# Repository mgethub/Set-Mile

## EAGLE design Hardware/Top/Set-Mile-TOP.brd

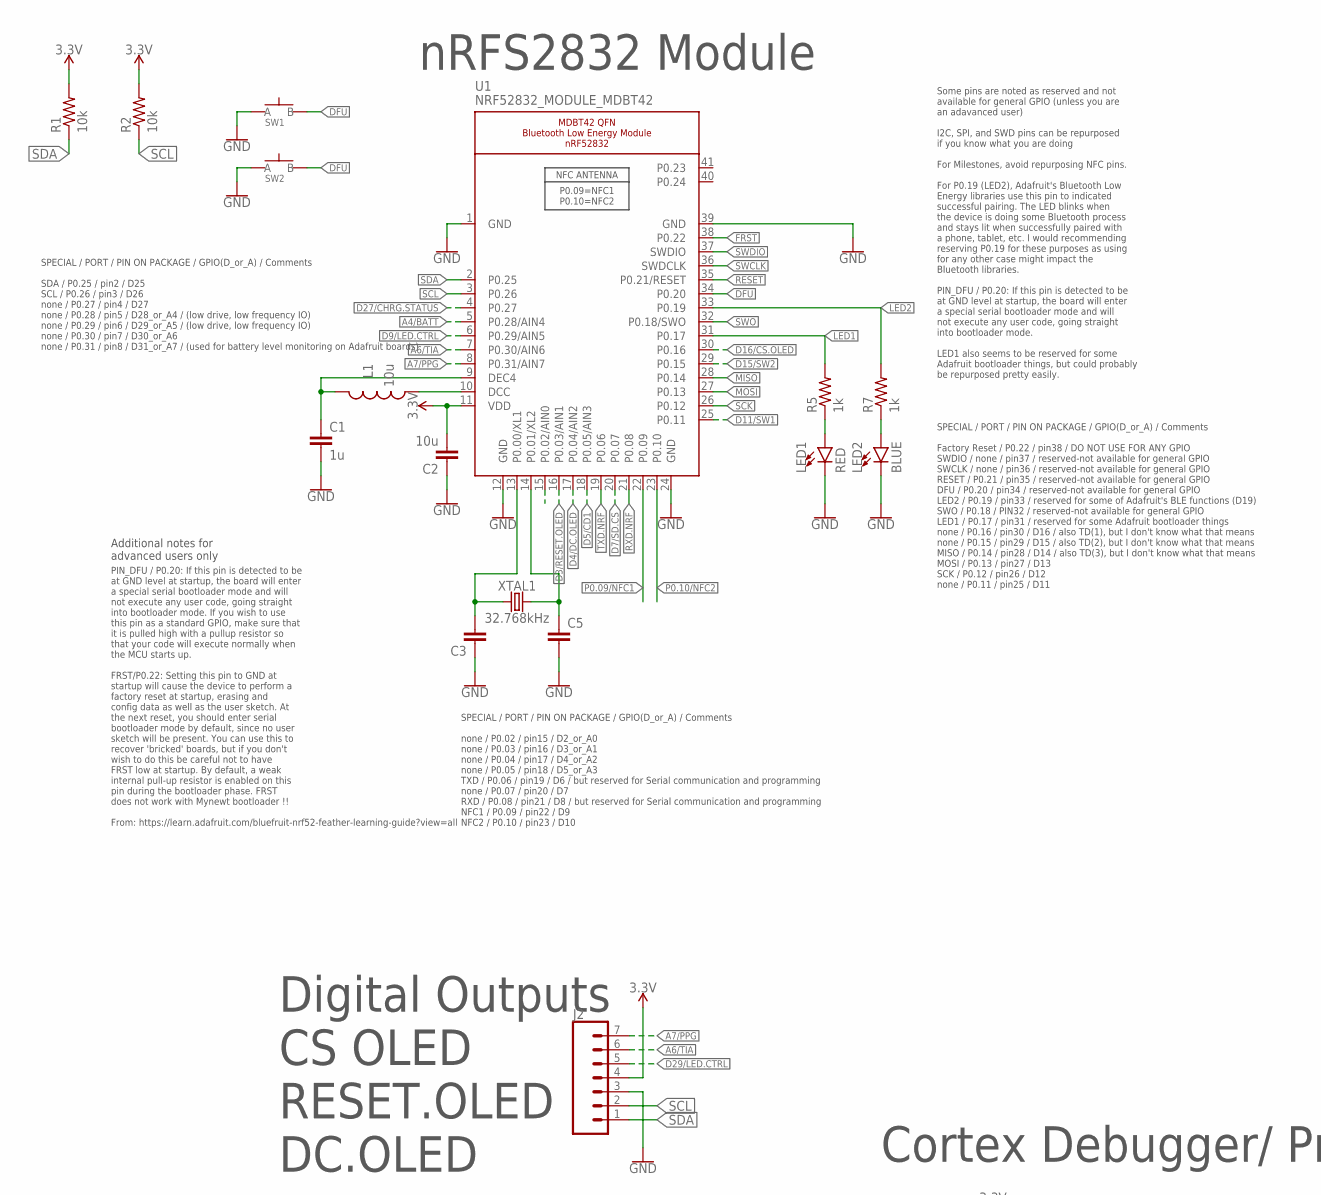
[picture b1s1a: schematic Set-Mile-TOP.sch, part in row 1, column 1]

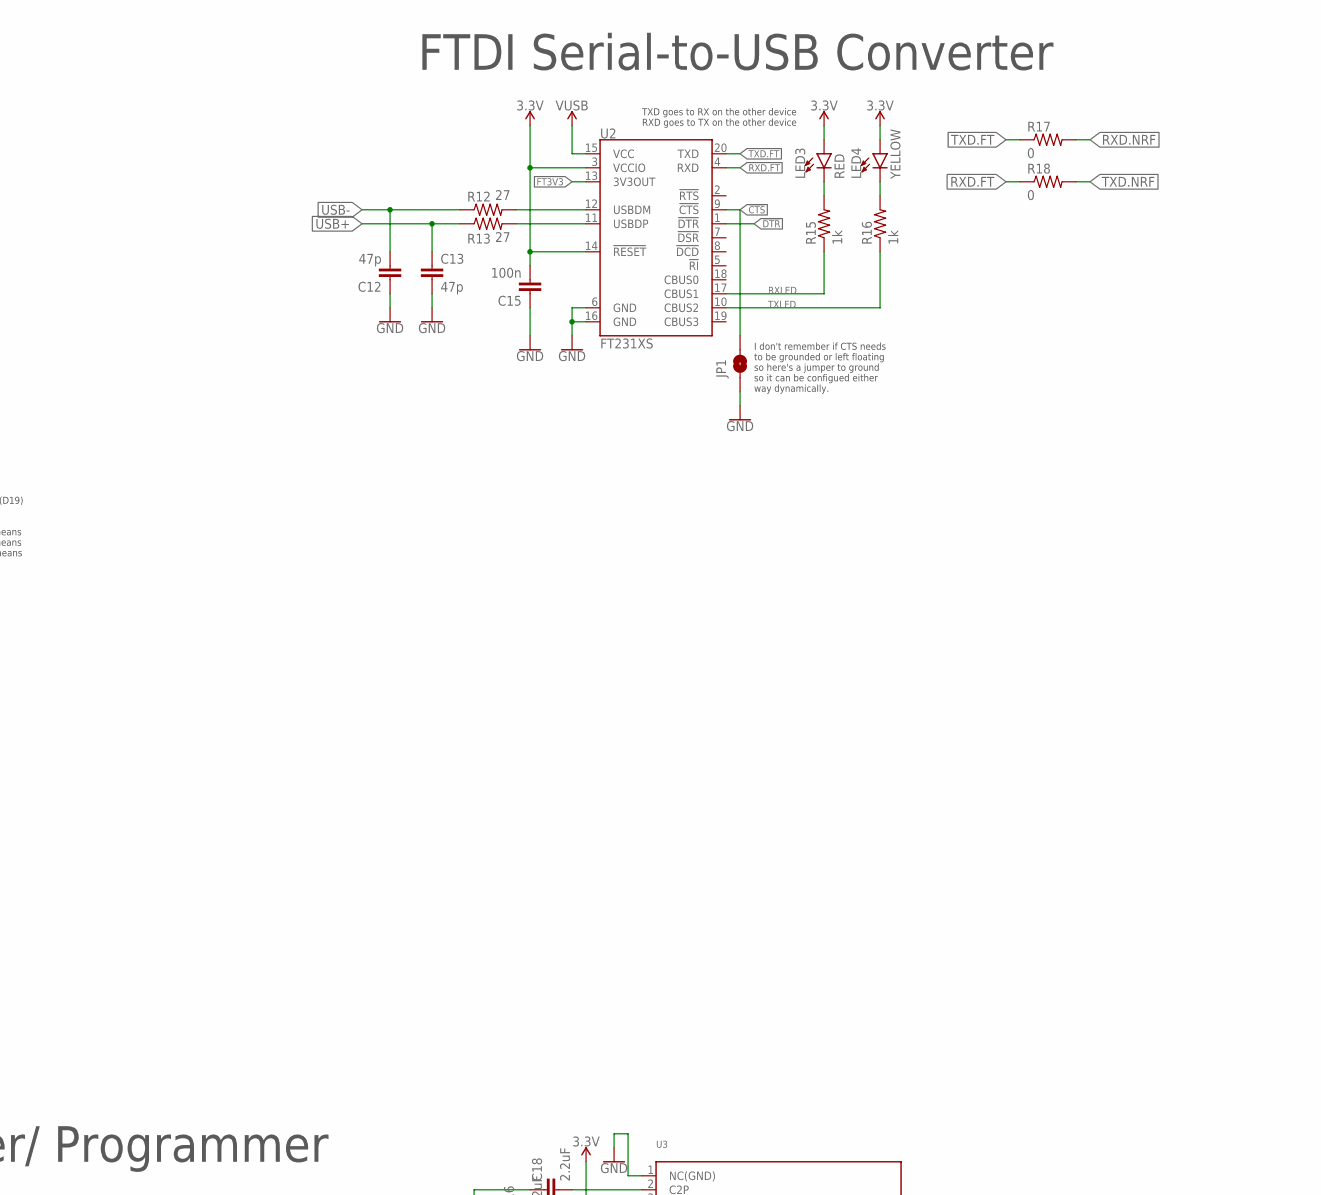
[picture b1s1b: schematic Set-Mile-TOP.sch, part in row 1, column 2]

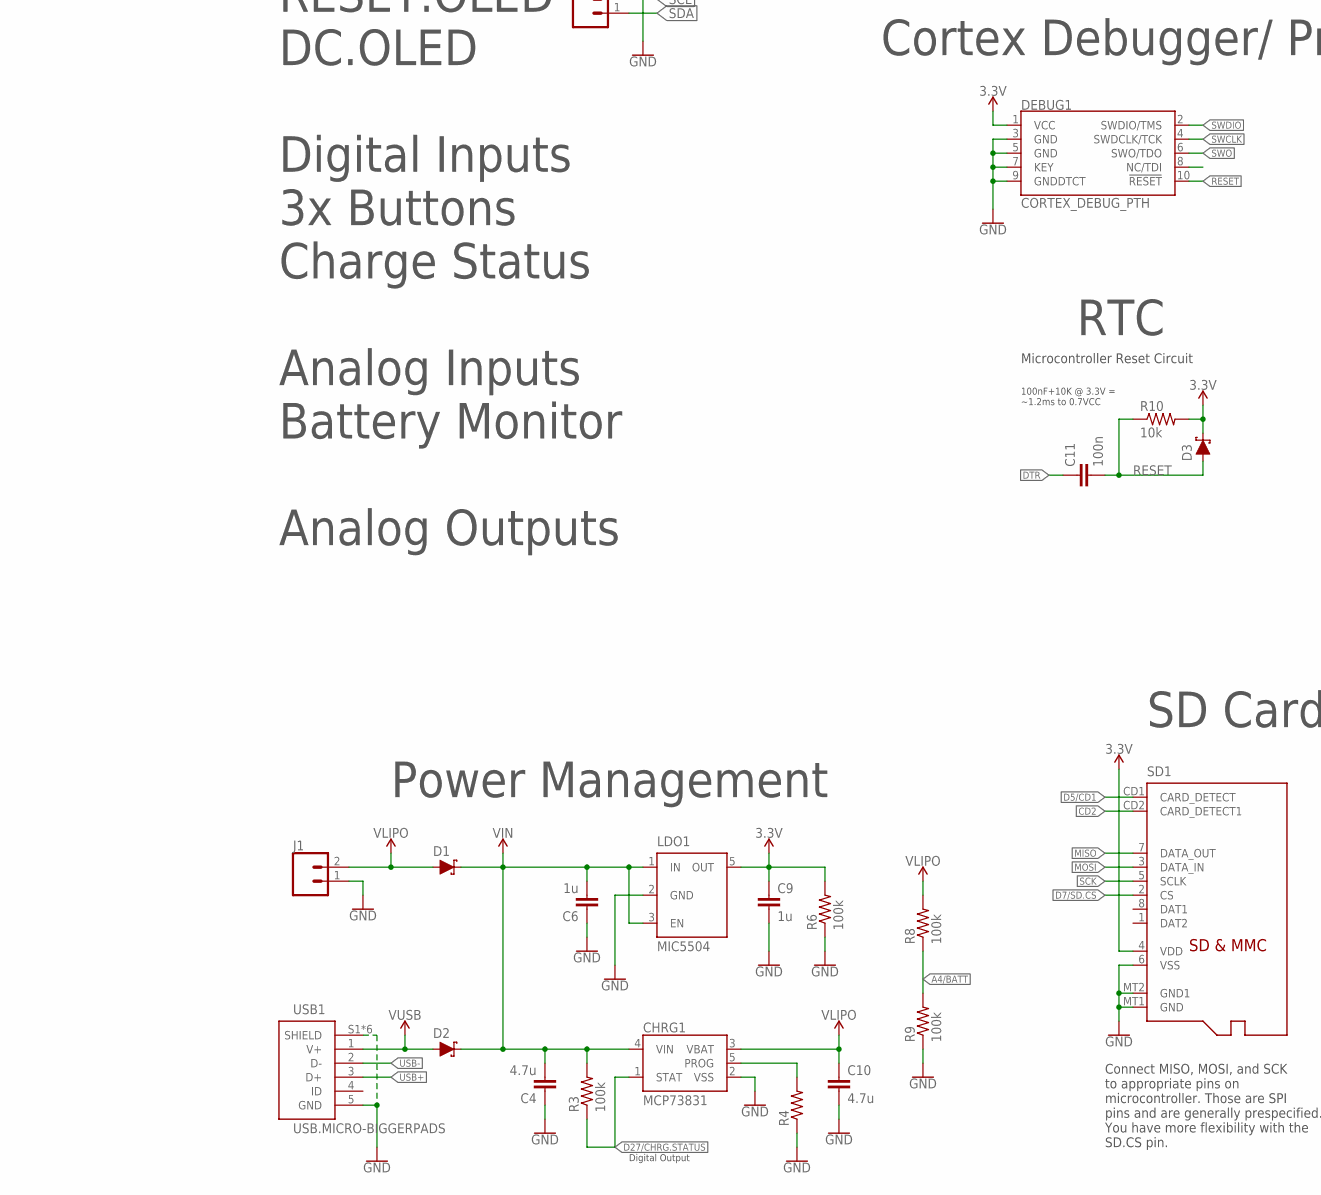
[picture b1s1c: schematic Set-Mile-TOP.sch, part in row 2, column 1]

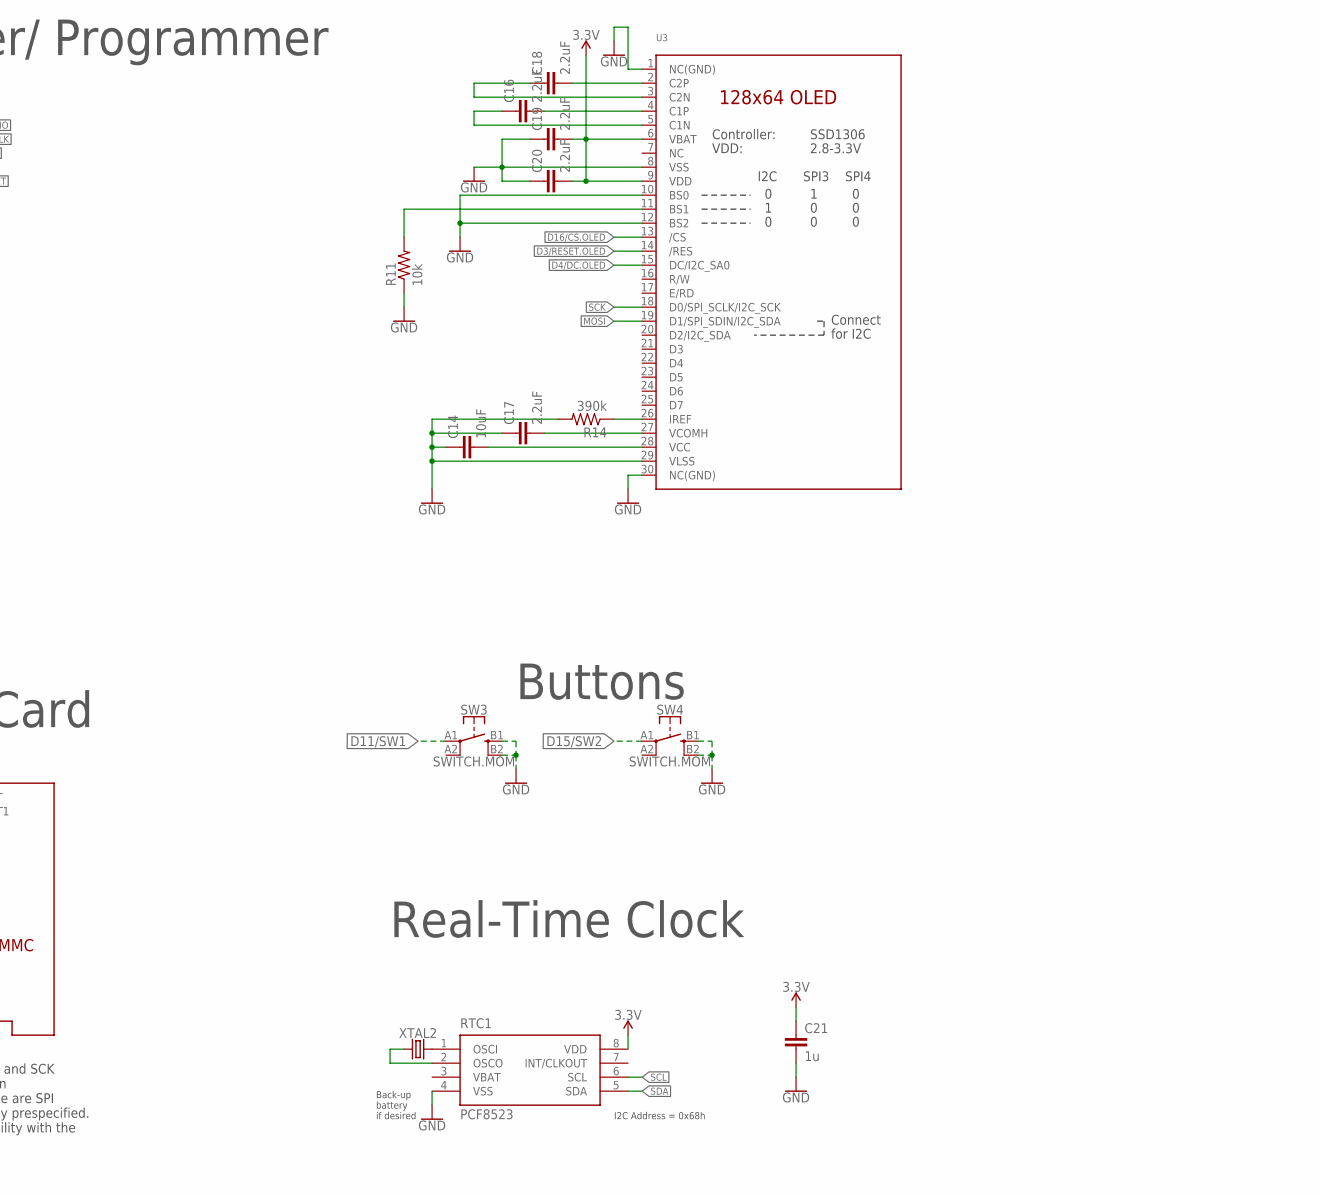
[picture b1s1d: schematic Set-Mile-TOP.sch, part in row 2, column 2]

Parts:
C1, C6, C9, C21: 1u; C0603
C2: 10u; C0805
C3, C5: CAPACITOR0603; C0603
C4, C10: 4.7u; C0603
C11, C15: 100n; C0603
C12, C13: 47p; C0603
C14: 10uF; C0603
C16, C17, C18, C19, C20: 2.2uF; C0402
CHRG1: MCP73831; SOT23-5
D1, D2, D3: SCHOTTKY-USC; USC
DEBUG1: CORTEX_DEBUG_PTH; 2X5-PTH-1.27MM
J1: CONN_02; 1X02
J2: CONN_07-1.27MM; 1X07_1.27MM
JP1: JUMPER-SMT_2_NO_SILK; SMT-JUMPER_2_NO_SILK
L1: 10u; L0603
LDO1: MIC5504; SOT23-5
LED1, LED3: RED; LED-0603
LED2: BLUE; LED-0603
LED4: YELLOW; LED-0603
R1, R2, R10, R11: 10k; R0603
R3, R6, R8, R9: 100k; R0603
R4: RESISTOR0603; R0603
R5, R7, R15, R16: 1k; R0603
R12, R13: 27; R0603
R14: 390k; R0603
R17, R18: 0; R0603
RTC1: PCF8523; SO8; DIGIKEY 568-5306-1-ND
SD1: MICROSD
SW1, SW2: SPST-PTS830GG140-COPY.1-3; BUTTON-GULLWING
SW3, SW4: SWITCH.MOM; TACTILE_SWITCH_SMD_6.2MM_TALL
U1: NRF52832_MODULE_MDBT42; BLE_MODULE_RAYTAC_MDBT42
U2: FT231XS; SSOP20_L
U3: DISP_OLED_UG-2864HSWEG01-NO-WRAPAROUND; UG-2864HSWEG01_0.96IN_NO-WRAPAROUND
USB1: USB.MICRO-BIGGERPADS; USB-MICRO-01.BIGGERPADS
XTAL1: 32.768kHz; 2-SMD.NOLEAD.2.0MMTO1.2MM
XTAL2: 32.7680kHz; 2-SMD.NOLEAD.2.0MMTO1.2MM

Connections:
3.3V: C2.2, C9.1, C15.2, C19.2, C20.2, C21.1, D3.- (C), DEBUG1.1 (VCC), J2.4, LDO1.5 (OUT), LED3.A, LED4.A, R1.2, R2.2, R6.2, R10.2, RTC1.8 (VDD), SD1.4 (VDD), U1.11 (VDD), U2.3 (VCCIO), U2.14 (!RESET), U3.6 (VBAT), U3.9 (VDD)
!CTS: JP1.2, U2.9 (!CTS)
!DTR: U2.1 (!DTR)
A4/BATT: R8.1, R9.2, U1.5 (P0.28/AIN4)
A6/TIA: J2.6, U1.7 (P0.30/AIN6)
A7/PPG: J2.7, U1.8 (P0.31/AIN7)
CD2: SD1.CD2 (CARD_DETECT1)
D3/RESET.OLED: U1.16 (P0.03/AIN1), U3.14 (/RES)
D4/DC.OLED: U1.15 (P0.02/AIN0), U1.17 (P0.04/AIN2), U3.15 (DC/I2C_SA0)
D5/CD1: SD1.CD1 (CARD_DETECT), U1.18 (P0.05/AIN3)
D7/SD.CS: SD1.2 (CS), U1.20 (P0.07)
D9/LED.CTRL: U1.6 (P0.29/AIN5)
D11/SW1: SW3.A1 (1), U1.25 (P0.11)
D15/SW2: SW4.A1 (1), U1.29 (P0.15)
D16/CS.OLED: U1.30 (P0.16), U3.13 (/CS)
D27/CHRG.STATUS: CHRG1.1 (STAT), R3.1, U1.4 (P0.27)
D29/LED.CTRL: J2.5
DFU: SW1.3 (B), SW2.3 (B), U1.34 (P0.20)
DTR: C11.1
FRST: U1.38 (P0.22)
FT3V3: U2.13 (3V3OUT)
GND: C1.2, C2.1, C3.1, C4.1, C5.2, C6.1, C9.2, C10.2, C12.1, C13.2, C14.1, C15.1, C17.1, C19.1, C20.1, C21.2, CHRG1.2 (VSS), DEBUG1.3 (GND), DEBUG1.5 (GND), DEBUG1.7 (KEY), DEBUG1.9 (GNDDTCT), J1.1, J2.3, JP1.1, LDO1.2 (GND), LED1.C, LED2.C, R4.1, R6.1, R9.1, R11.1, R14.2, RTC1.4 (VSS), SD1.6 (VSS), SD1.MT1 (GND), SD1.MT2 (GND1), SW1.1 (A), SW2.1 (A), SW3.B1 (3), SW3.B2 (4), SW4.B1 (3), SW4.B2 (4), U1.1 (GND), U1.12 (GND), U1.24 (GND), U1.39 (GND), U2.6 (GND), U2.16 (GND), U3.1 (NC(GND)), U3.8 (VSS), U3.10 (BS0), U3.12 (BS2), U3.29 (VLSS), U3.30 (NC(GND)), USB1.5 (GND), USB1.S1 (SHIELD), USB1.S2 (SHIELD), USB1.S3 (SHIELD), USB1.S4 (SHIELD), USB1.S5 (SHIELD), USB1.S6 (SHIELD)
LED1: R5.2, U1.31 (P0.17)
LED2: R7.2, U1.33 (P0.19)
MISO: SD1.7 (DATA_OUT), U1.28 (P0.14)
MOSI: SD1.3 (DATA_IN), U1.27 (P0.13), U3.19 (D1/SPI_SDIN/I2C_SDA)
unnamed: R11.2, U3.11 (BS1)
unnamed: R14.1, U3.26 (IREF)
unnamed: C18.2, U3.2 (C2P)
unnamed: C3.2, U1.13 (P0.00/XL1), XTAL1.P$1 (1)
unnamed: C18.1, U3.3 (C2N)
unnamed: C5.1, U1.14 (P0.01/XL2), XTAL1.P$2 (2)
unnamed: C16.2, U3.4 (C1P)
unnamed: C16.1, U3.5 (C1N)
unnamed: LED1.A, R5.1
unnamed: LED2.A, R7.1
unnamed: L1.1, U1.10 (DCC)
unnamed: C1.1, L1.2, U1.9 (DEC4)
unnamed: C14.2, U3.28 (VCC)
unnamed: C17.2, U3.27 (VCOMH)
unnamed: CHRG1.5 (PROG), R4.2
unnamed: RTC1.2 (OSCO), XTAL2.P$1 (1)
unnamed: RTC1.1 (OSCI), XTAL2.P$2 (2)
unnamed: R12.2, U2.12 (USBDM)
unnamed: R13.2, U2.11 (USBDP)
unnamed: LED3.C, R15.2
unnamed: LED4.C, R16.2
P0.09/NFC1: U1.22 (P0.09)
P0.10/NFC2: U1.23 (P0.10)
RESET: C11.2, D3.+ (A), DEBUG1.10 (!RESET), R10.1, U1.35 (P0.21/RESET)
RXD.FT: R18.1, U2.4 (RXD)
RXD.NRF: R17.2, U1.21 (P0.08)
RXLED: R15.1, U2.17 (CBUS1)
SCK: SD1.5 (SCLK), U1.26 (P0.12), U3.18 (D0/SPI_SCLK/I2C_SCK)
SCL: J2.2, R2.1, RTC1.6 (SCL), U1.3 (P0.26)
SDA: J2.1, R1.1, RTC1.5 (SDA), U1.2 (P0.25)
SWCLK: DEBUG1.4 (SWDCLK/TCK), U1.36 (SWDCLK)
SWDIO: DEBUG1.2 (SWDIO/TMS), U1.37 (SWDIO)
SWO: DEBUG1.6 (SWO/TDO), U1.32 (P0.18/SWO)
TXD.FT: R17.1, U2.20 (TXD)
TXD.NRF: R18.2, U1.19 (P0.06)
TXLED: R16.1, U2.10 (CBUS2)
USB+: C13.1, R13.1, USB1.3 (D+)
USB-: C12.2, R12.1, USB1.2 (D-)
VIN: C4.2, C6.2, CHRG1.4 (VIN), D1.- (C), D2.- (C), LDO1.1 (IN), LDO1.3 (EN), R3.2
VLIPO: C10.1, CHRG1.3 (VBAT), D1.+ (A), J1.2, R8.2
V_USB: D2.+ (A), U2.15 (VCC), USB1.1 (V+)

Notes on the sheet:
Microcontroller Reset Circuit
100nF+10K @ 3.3V = ~1.2ms to 0.7VCC
SPECIAL / PORT / PIN ON PACKAGE / GPIO(D_or_A) / Comments SDA / P0.25 / pin2 / D25 SCL / P0.26 / pin3 / D26 none / P0.27 / pin4 / D27 none / P0.28 / pin5 / D28_or_A4 / (low drive, low frequency IO) none / P0.29 / pin6 / D29_or_A5 / (low drive, low frequency IO) none / P0.30 / pin7 / D30_or_A6 none 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
SPECIAL / PORT / PIN ON PACKAGE / GPIO(D_or_A) / Comments none / P0.02 / pin15 / D2_or_A0 none / P0.03 / pin16 / D3_or_A1 none / P0.04 / pin17 / D4_or_A2 none / P0.05 / pin18 / D5_or_A3 TXD / P0.06 / pin19 / D6 / but reserved for Serial communication and programming none / P0.07 / pin20 / D7 RXD / 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
SPECIAL / PORT / PIN ON PACKAGE / GPIO(D_or_A) / Comments Factory Reset / P0.22 / pin38 / DO NOT USE FOR ANY GPIO SWDIO / none / pin37 / reserved-not available for general GPIO SWCLK / none / pin36 / reserved-not available for general GPIO RESET / P0.21 / pin35 / reserved-not available for general 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
Some pins are noted as reserved and not available for general GPIO (unless you are an adavanced user) I2C, SPI, and SWD pins can be repurposed if you know what you are doing For Milestones, avoid repurposing NFC pins. For P0.19 (LED2), Adafruit's Bluetooth Low Energy libraries use this pin to indic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
PIN_DFU / P0.20: If this pin is detected to be at GND level at startup, the board will enter a special serial bootloader mode and will not execute any user code, going straight into bootloader mode. If you wish to use this pin as a standard GPIO, make sure that it is pulled high with a pullup resis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
Additional notes for advanced users only
Connect MISO, MOSI, and SCK to appropriate pins on microcontroller. Those are SPI pins and are generally prespecified. You have more flexibility with the SD.CS pin.
I2C Address = 0x68h
Back-up battery if desired
SD Card
nRFS2832 Module
Real-Time Clock
RTC
Cortex Debugger/ Programmer
Power Management
Buttons
Digital Outputs CS OLED RESET.OLED DC.OLED Digital Inputs 3x Buttons Charge Status Analog Inputs Battery Monitor Analog Outputs
TXD goes to RX on the other device RXD goes to TX on the other device
I don't remember if CTS needs to be grounded or left floating so here's a jumper to ground so it can be configued either way dynamically.
FTDI Serial-to-USB Converter
Digital Output

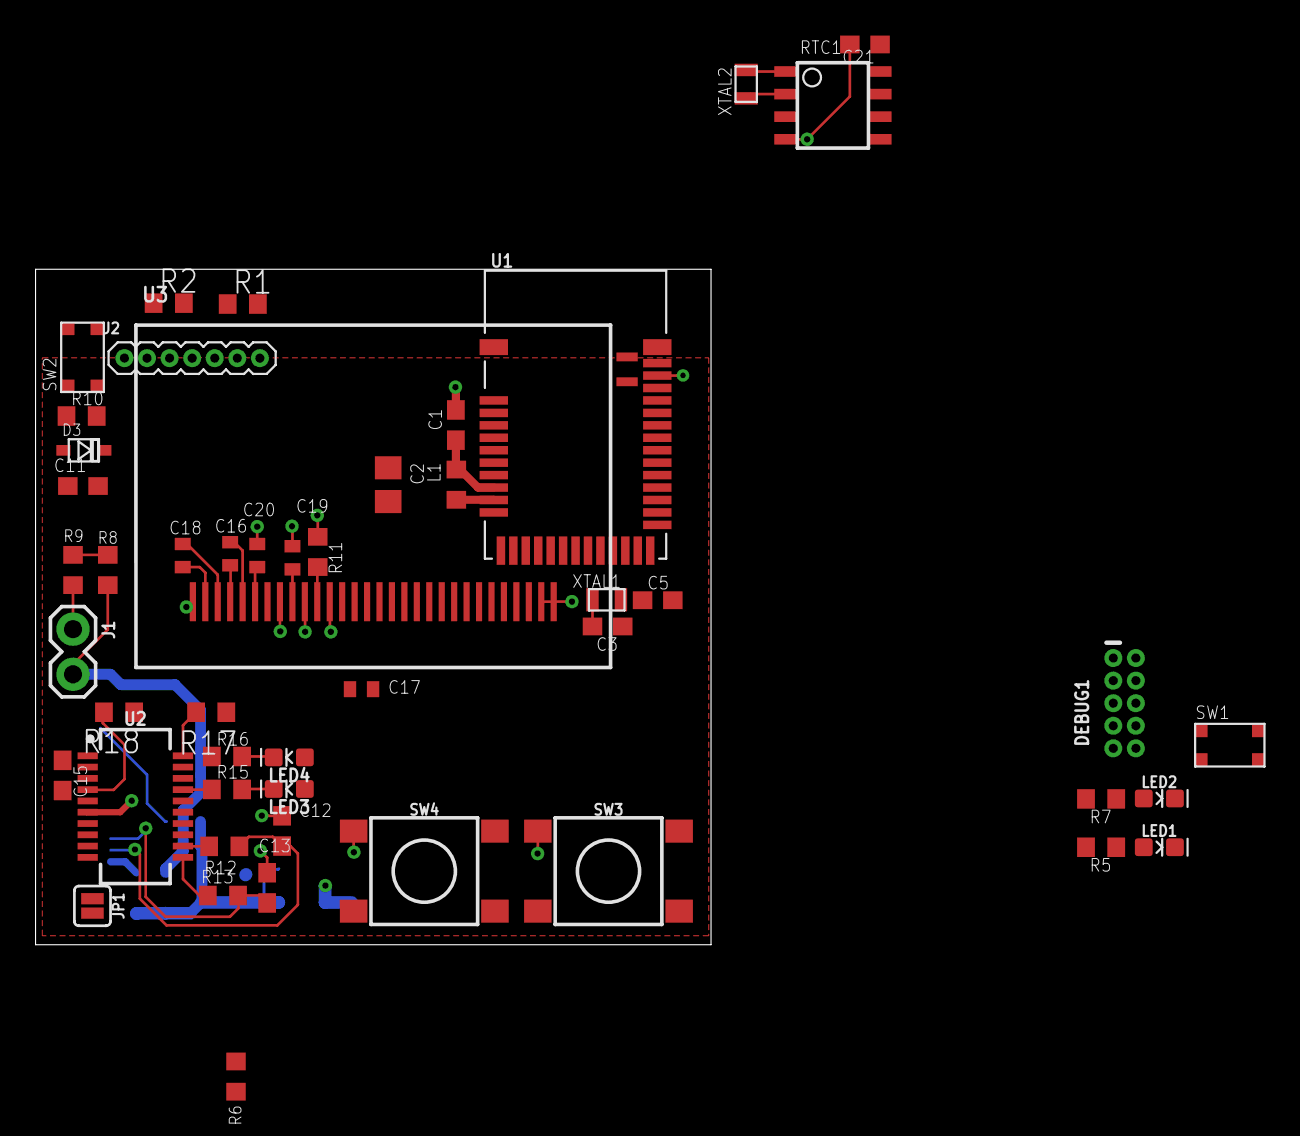
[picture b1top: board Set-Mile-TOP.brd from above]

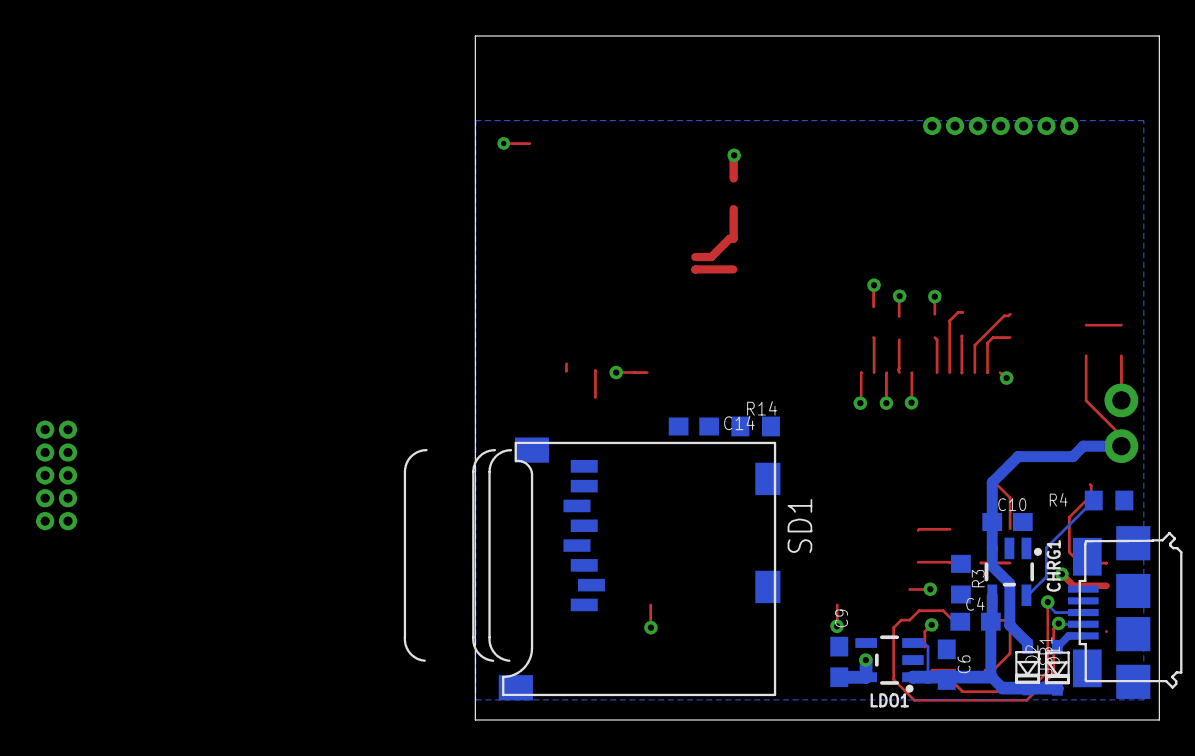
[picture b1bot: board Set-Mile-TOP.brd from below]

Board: 2 copper layers, 38.0 x 38.0 mm, 63 parts (14 on the bottom side), 58 nets.

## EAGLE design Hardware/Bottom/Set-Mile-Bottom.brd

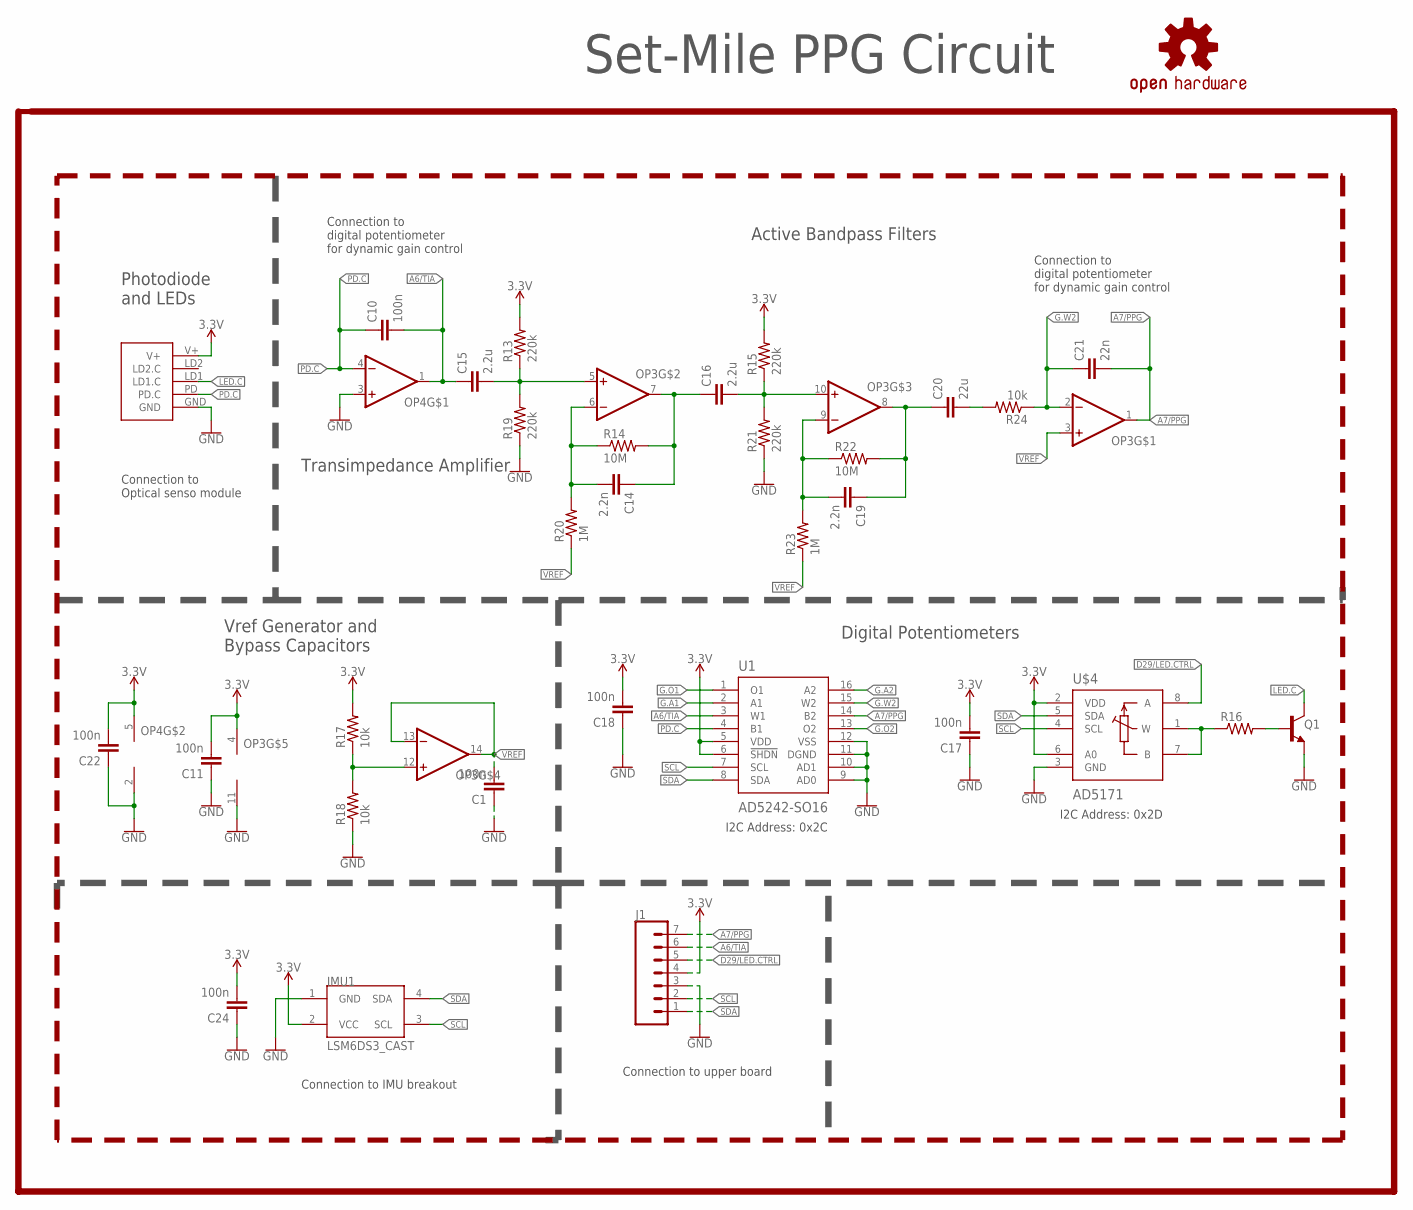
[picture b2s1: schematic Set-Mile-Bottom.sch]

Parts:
C1, C10, C11, C17, C18, C22, C24: 100n; C0603
C14, C19: 2.2n; C0603
C15, C16: 2.2u; C0603
C20: 22u; C0603
C21: 22n; C0603
IMU1: LSM6DS3_CAST
J1: CONN_07-1.27MM; 1X07_1.27MM
LOGO1: REVISION.A; REV.A
LOGO2: OSHW-LOGOL; OSHW-LOGO-L
OP3: OP-QUAD-SO14; SO14
OP4: OP-SINGLEOT; SOT23-5
Q1: NPN-GENERIC; SOT23-3
R13, R15, R19, R21: 220k; R0603
R14, R22: 10M; R0603
R16: RESISTOR0603; R0603
R17, R18: 10k; R0402
R20, R23: 1M; R0603
R24: 10k; R0603
U1: AD5242-SO16; SO16
U$3: PPG.MODULE.2
U$4: AD5171; SOT-23-8

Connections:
3.3V: C11.2, C17.2, C18.2, C22.2, C24.2, IMU1.2 (VCC), J1.4, OP3.4 (V+), OP4.5 (V+), R13.2, R15.2, R17.2, U1.5 (VDD), U1.6 (!SHDN), U$3.V+, U$4.2 (VDD), U$4.6 (A0)
A6/TIA: C10.2, C15.1, J1.6, OP4.1 (OUT), U1.3 (W1)
A7/PPG: C21.2, J1.7, OP3.1 (OUT), U1.14 (B2)
D29/LED.CTRL: J1.5, U$4.8 (A)
G.A1: U1.2 (A1)
G.A2: U1.16 (A2)
G.O1: U1.1 (O1)
G.O2: U1.13 (O2)
G.W2: C21.1, OP3.2 (-IN), R24.1, U1.15 (W2)
GND: C1.1, C11.1, C17.1, C18.1, C22.1, C24.1, IMU1.1 (GND), J1.3, OP3.11 (V-), OP4.2 (V-), OP4.3 (+IN), Q1.2 (E), R18.1, R19.1, R21.1, U1.9 (AD0), U1.10 (AD1), U1.11 (DGND), U1.12 (VSS), U$3.GND, U$4.3 (GND)
LED.C: Q1.3 (C), U$3.LD1 (LD1.C)
unnamed: Q1.1 (B), R16.2
unnamed: R16.1, U$4.1 (W), U$4.7 (B)
unnamed: OP3.12 (+IN), R17.1, R18.2
unnamed: C15.2, OP3.5 (+IN), R13.1, R19.2
unnamed: C14.2, OP3.6 (-IN), R14.1, R20.2
unnamed: C14.1, C16.1, OP3.7 (OUT), R14.2
unnamed: C16.2, OP3.10 (+IN), R15.1, R21.2
unnamed: C19.2, OP3.9 (-IN), R22.1, R23.2
unnamed: C19.1, C20.1, OP3.8 (OUT), R22.2
unnamed: C20.2, R24.2
PD.C: C10.1, OP4.4 (-IN), U1.4 (B1), U$3.PD (PD.C)
SCL: IMU1.3 (SCL), J1.2, U1.7 (SCL), U$4.4 (SCL)
SDA: IMU1.4 (SDA), J1.1, U1.8 (SDA), U$4.5 (SDA)
VREF: C1.2, OP3.3 (+IN), OP3.13 (-IN), OP3.14 (OUT), R20.1, R23.1

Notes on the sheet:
Photodiode and LEDs
Active Bandpass Filters
Digital Potentiometers
Transimpedance Amplifier
I2C Address: 0x2C
I2C Address: 0x2D
Connection to Optical senso module
Connection to digital potentiometer for dynamic gain control
Connection to upper board
Connection to IMU breakout
Vref Generator and Bypass Capacitors
Set-Mile PPG Circuit

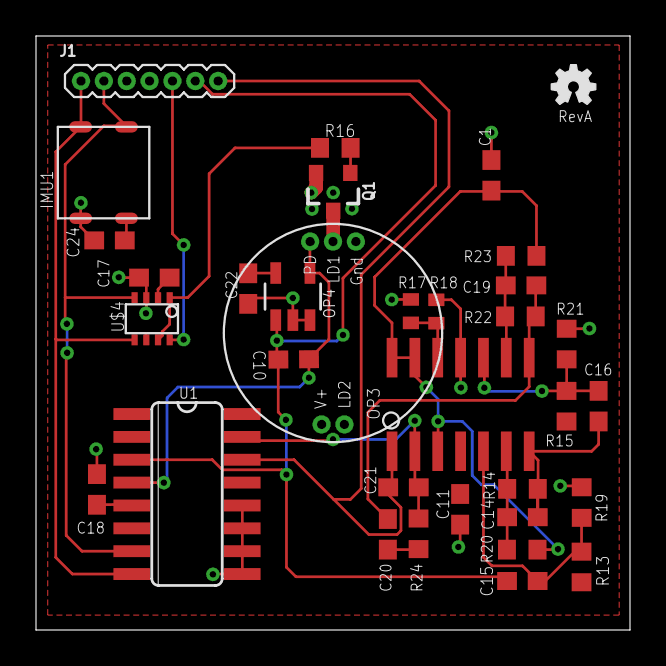
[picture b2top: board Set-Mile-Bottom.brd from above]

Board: 2 copper layers, 33.0 x 33.0 mm, 36 parts (0 on the bottom side), 21 nets.

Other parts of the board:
U$1: OSHW-LOGO-MINI

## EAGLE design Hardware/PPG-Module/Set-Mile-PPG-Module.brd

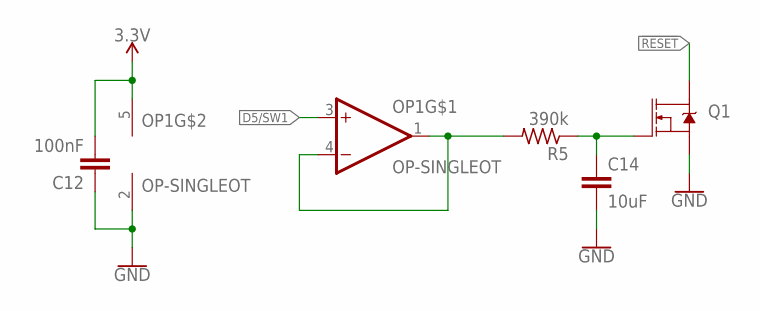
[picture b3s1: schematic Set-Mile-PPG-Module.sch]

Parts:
C12: 100nF; C0603
C14: 10uF; C0805
OP1: OP-SINGLEOT; SOT23-5
Q1: 5.8A/30V/35mΩ; SOT23-3
R5: 390k; R0603

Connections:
3V: C12.2, OP1.5 (V+)
!RESET: Q1.3 (D)
D5/SW1: OP1.3 (+IN)
GND: C12.1, C14.2, OP1.2 (V-), Q1.2 (S)
unnamed: OP1.1 (OUT), OP1.4 (-IN), R5.2
unnamed: C14.1, Q1.1 (G), R5.1

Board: 2 copper layers, 5 parts (0 on the bottom side), 4 nets, no tracks yet.

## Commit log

2020-05-29 feature list
2020-06-05 uploading organization folders
2020-06-05 added gitignore file
2020-06-05 changed dimension info the Docu layer
2020-06-05 copied BOM template
2020-06-11 Top Board Electronics Placed
2020-07-06 updated board design to section 2
2020-07-19 routing bottom board and oranized top board
